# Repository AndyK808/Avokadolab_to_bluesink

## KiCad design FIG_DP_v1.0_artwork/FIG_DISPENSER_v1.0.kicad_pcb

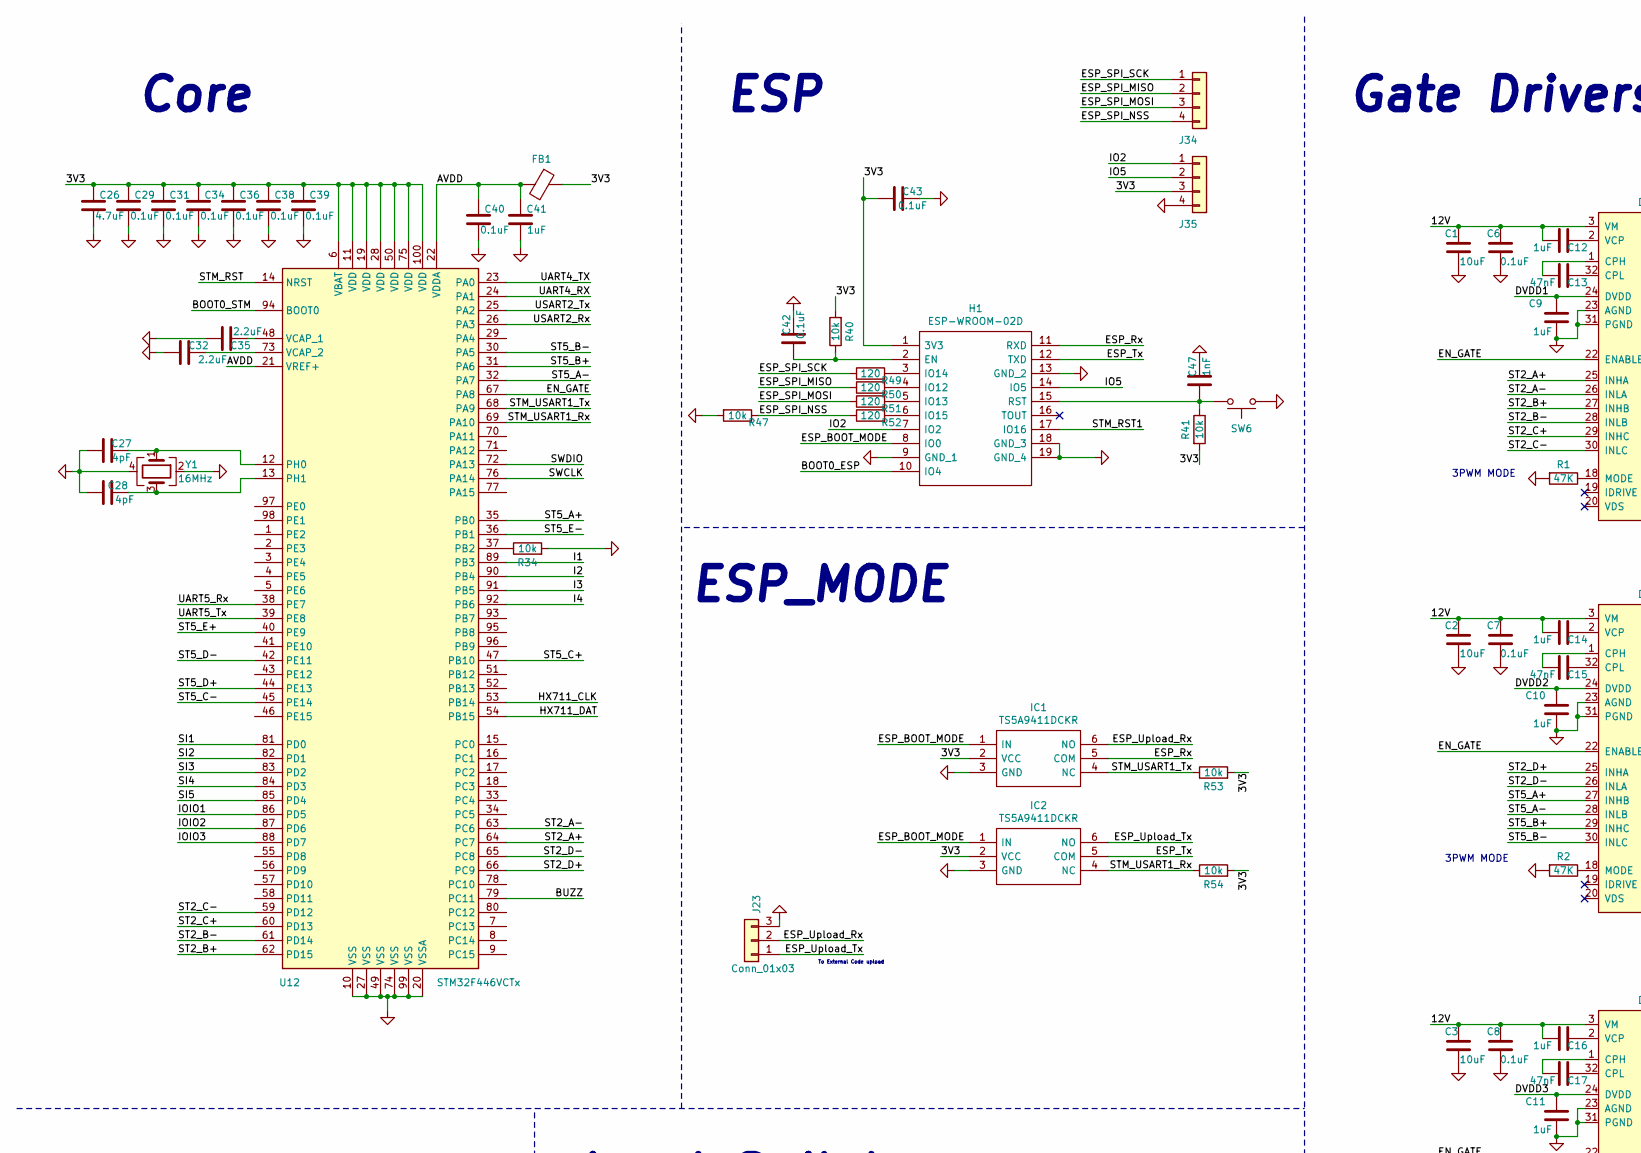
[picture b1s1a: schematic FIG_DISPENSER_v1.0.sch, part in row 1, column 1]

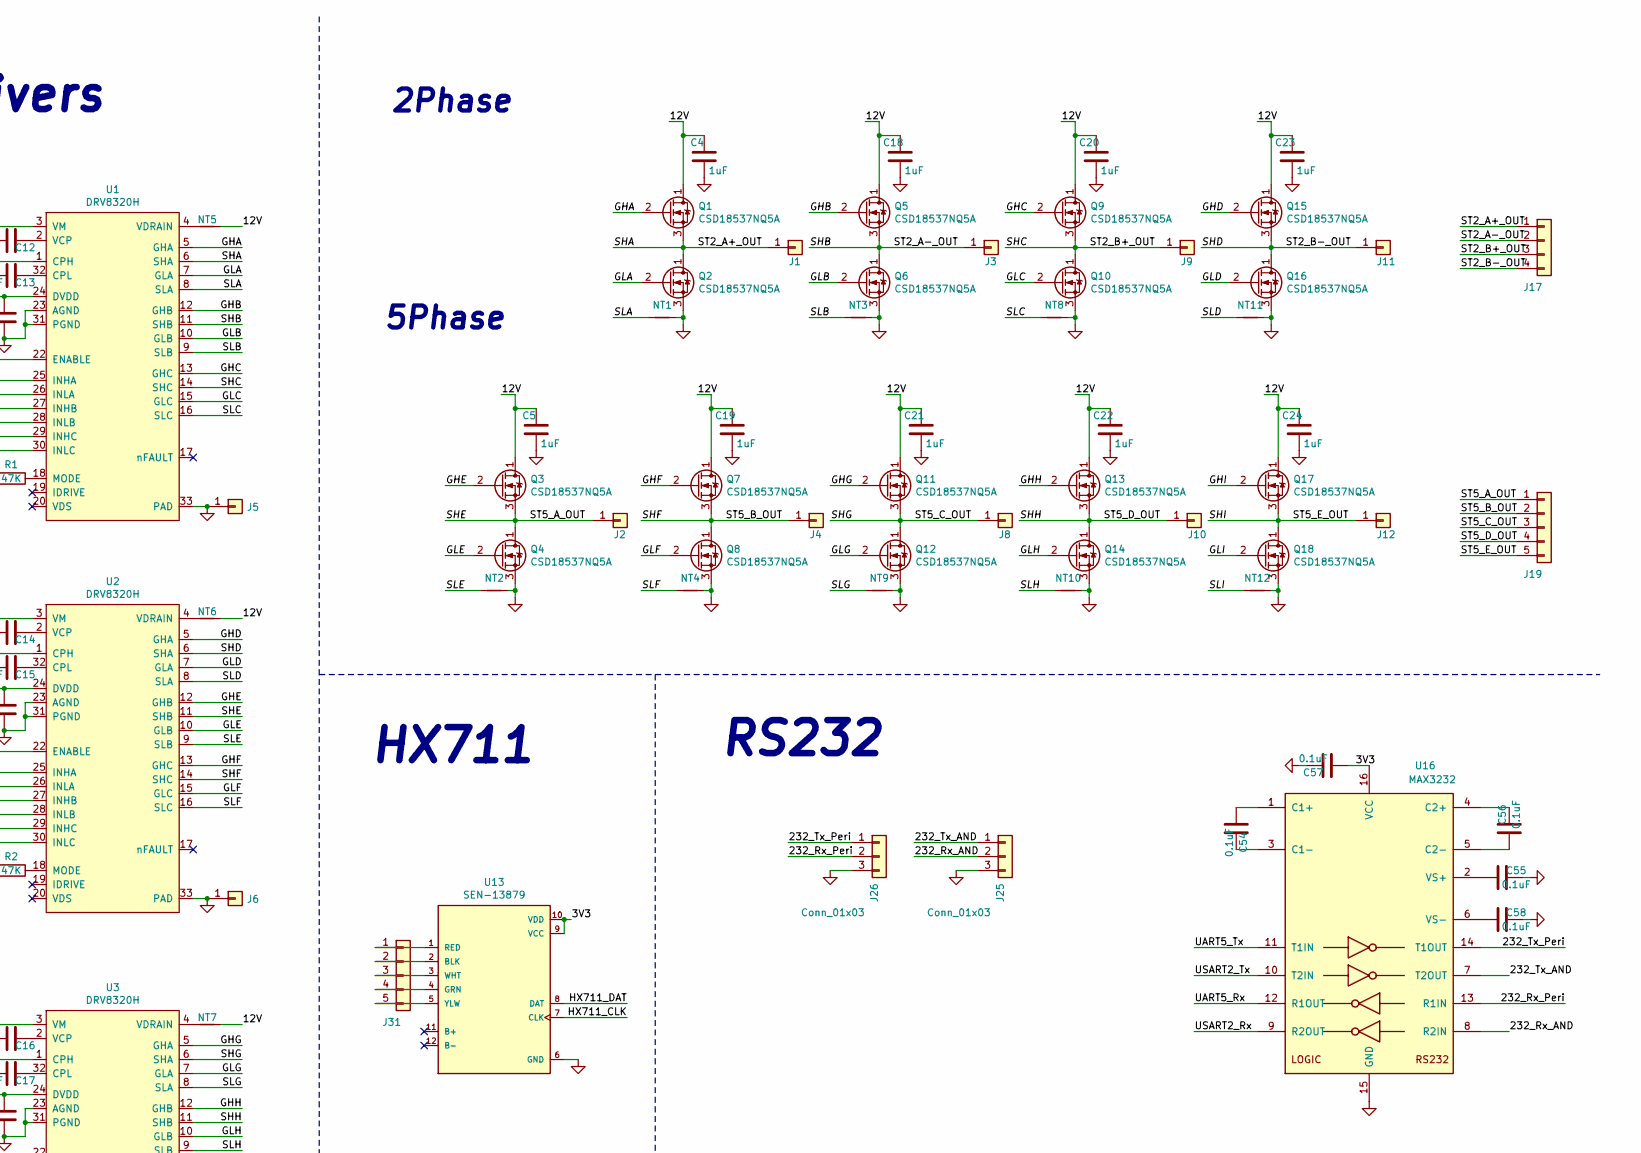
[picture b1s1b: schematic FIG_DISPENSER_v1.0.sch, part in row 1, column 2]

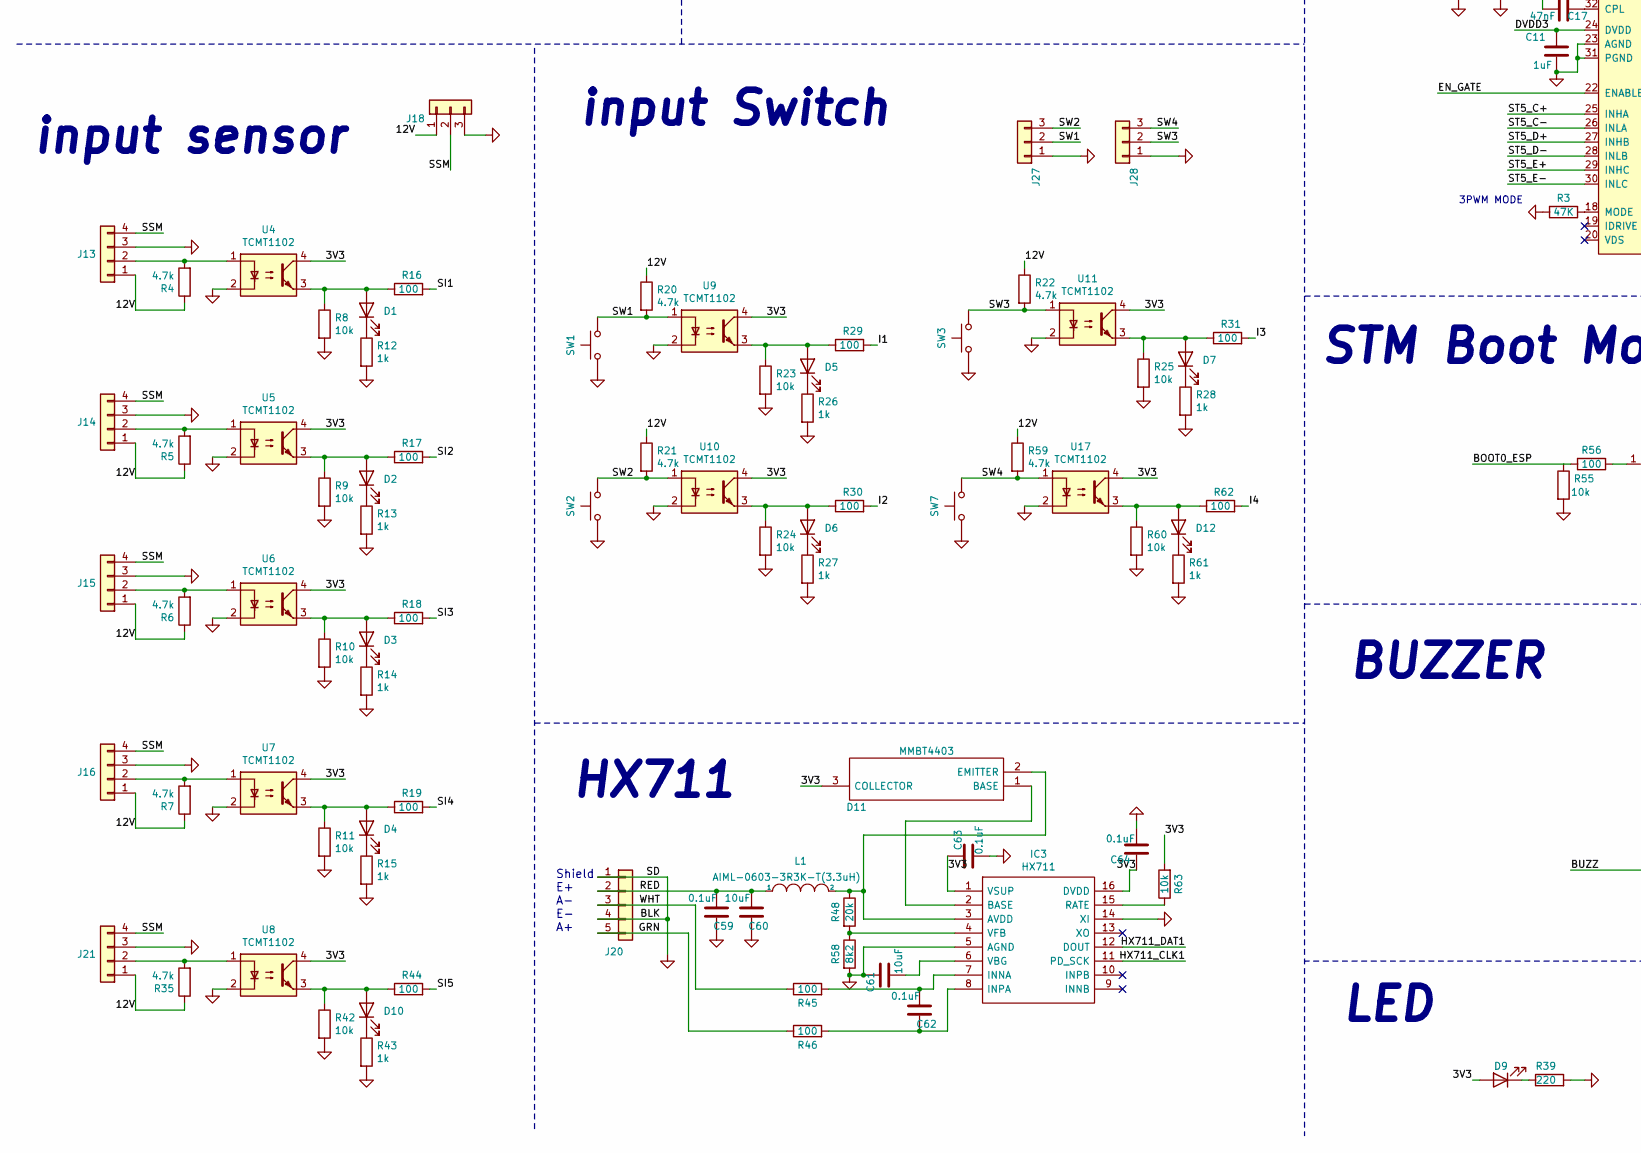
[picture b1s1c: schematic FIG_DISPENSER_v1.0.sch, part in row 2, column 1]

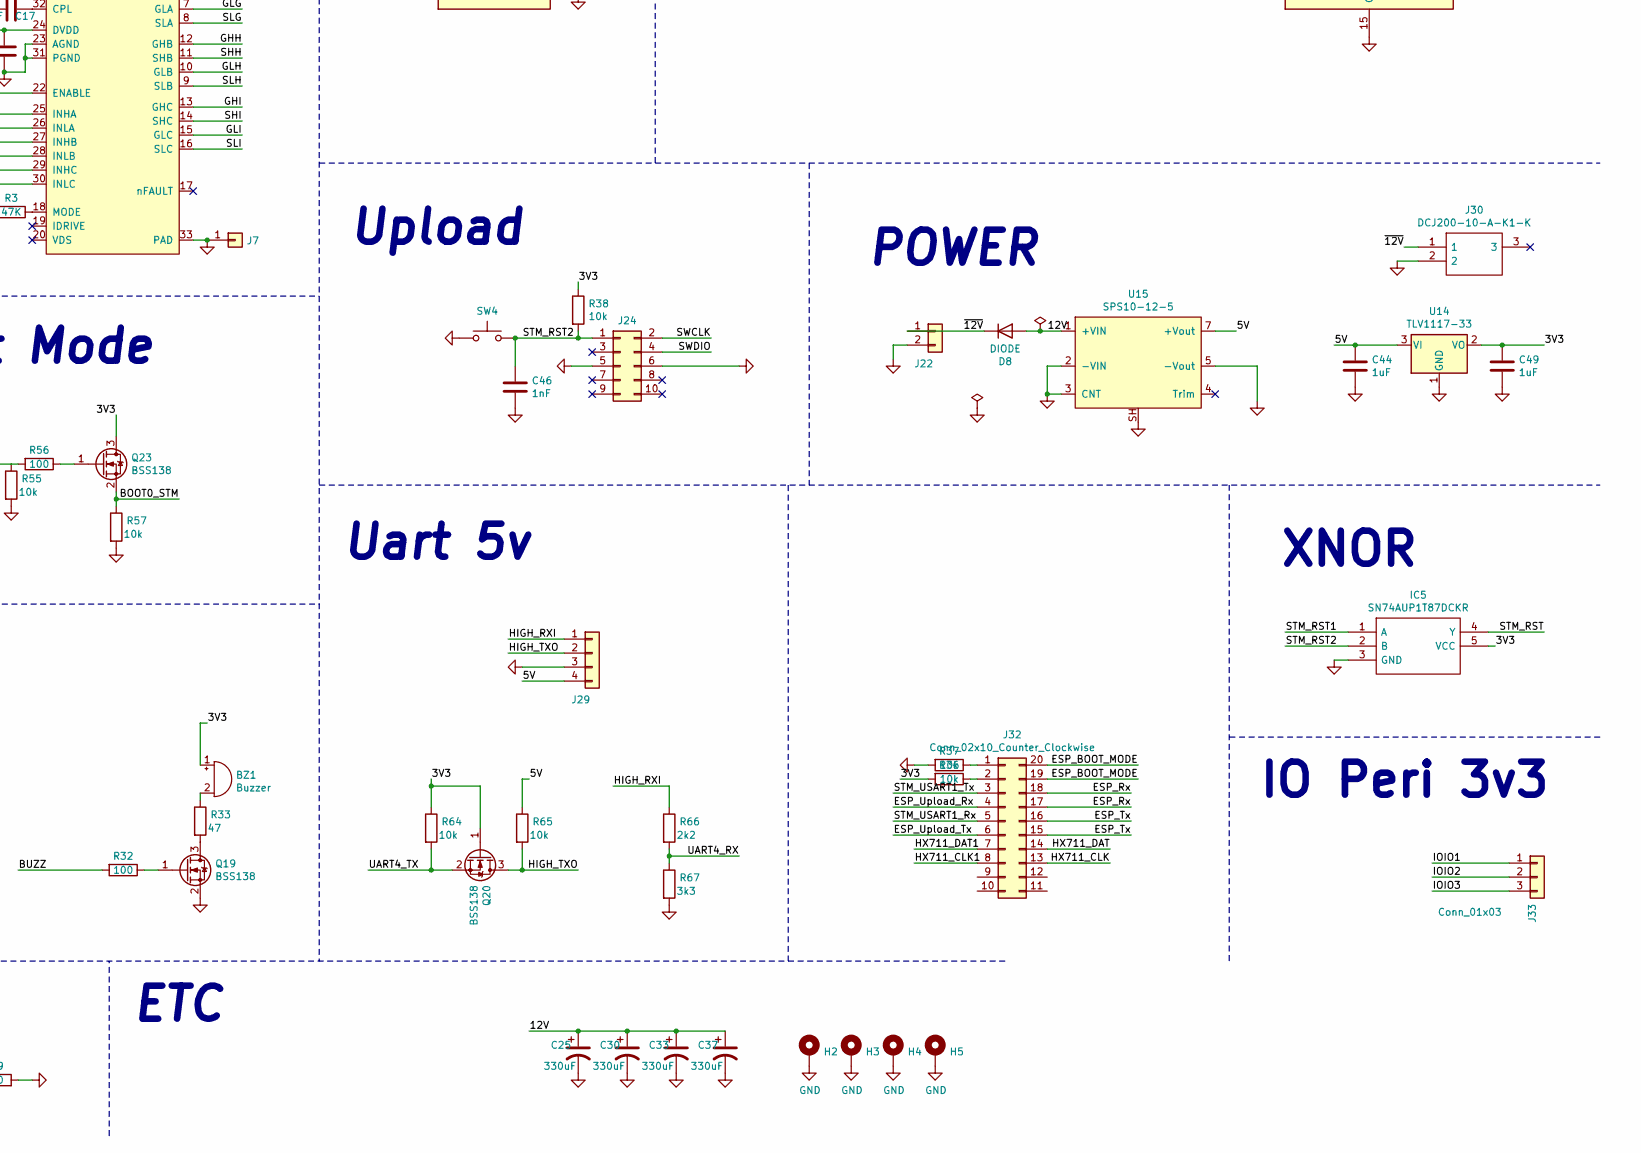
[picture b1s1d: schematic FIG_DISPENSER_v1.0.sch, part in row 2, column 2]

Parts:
BZ1: Buzzer; BUZZER
C1, C2, C3, C60, C61: 10uF; C_1206_3216Metric
C4, C5, C9, C10, C11, C12, C14, C16, C18, C19, C20, C21, C22, C23, C24, C44, C49: 1uF; C_0603_1608Metric
C6, C7, C8, C29, C42, C43, C54, C55, C56, C57, C58: 0.1uF; C_0603_1608Metric
C13, C15, C17: 47nF; C_0603_1608Metric
C25, C30, C33, C37: 330uF; CP_Radial_D10.0mm_P5.00mm
C26: 4.7uF; C_0603_1608Metric
C27, C28: 4pF; C_0603_1608Metric
C31, C34, C36, C38, C39, C40, C63, C64: 0.1uF; C_0402_1005Metric
C32, C35: 2.2uF; C_0603_1608Metric
C41: 1uF; C_0402_1005Metric
C46, C47: 1nF; C_0603_1608Metric
C59, C62: 0.1uF; C_1206_3216Metric
D1, D2, D3, D4, D5, D6, D7, D9, D10, D12: LED; LED_0603_1608Metric
D8: DIODE; D_DO-27_P15.24mm_Horizontal
D11: MMBT4403; SOT95P240X110-3N; Manufacturer_Part_Number MMBT4403; Mouser Part Number 583-MMBT4403
FB1: Ferrite_Bead; L_0603_1608Metric
H1: ESP-WROOM-02D; ESPWROOM02D; Manufacturer_Part_Number ESP-WROOM-02D; Mouser Part Number 356-ESPWROOM-02D
H2, H3, H4, H5: MountingHole_Pad; MountingHole_3mm_Pad_Via
IC1, IC2: TS5A9411DCKR; SOT65P210X110-6N; Mouser Part Number 595-TS5A9411DCKR
IC3: HX711; SOIC127P600X160-16N; Manufacturer_Part_Number HX711
IC5: SN74AUP1T87DCKR; SOT65P210X110-5N; Manufacturer_Part_Number SN74AUP1T87DCKR; Mouser Part Number 595-SN74AUP1T87DCKR
J1, J2, J3, J4, J5, J6, J7, J8, J9, J10, J11, J12: Conn_01x01; TestPoint_THTPad_D3.0mm_Drill1.5mm
J13, J14, J15, J16, J17, J21, J29, J34, J35: Conn_01x04; 5045-04
J18: Conn_01x03; PinHeader_1x03_P2.54mm_Vertical
J19, J20, J31: Conn_01x05; 5045-05
J22: Conn_01x02; LWB1143-02
J23, J25, J26, J27, J28, J33: Conn_01x03; 5045-03
J24: Conn_02x05_Odd_Even; IDC-Header_2x05_P2.54mm_Vertical
J30: DCJ200-10-A-K1-K; DCJ20010AK1K; Manufacturer_Part_Number DCJ200-10-A-K1-K
J32: Conn_02x10_Counter_Clockwise; slid_SW_SPST_10_array
L1: AIML-0603-3R3K-T(3.3uH); L_0603_1608Metric
NT1, NT2, NT3, NT4, NT5, NT6, NT7, NT8, NT9, NT10, NT11, NT12: Net-Tie_2; NET_TIE_0_25
Q1, Q2, Q3, Q4, Q5, Q6, Q7, Q8, Q9, Q10, Q11, Q12, Q13, Q14, Q15, Q16, Q17, Q18: CSD18537NQ5A
Q19, Q20, Q23: BSS138; SOT-23
R1, R2, R3: 47K; R_0603_1608Metric
R4, R5, R6, R7, R20, R21, R22, R35, R59: 4.7k; R_0603_1608Metric
R8, R9, R10, R11, R23, R24, R25, R34, R36, R37, R38, R40, R41, R42, R47, R53, R54, R55, R57, R60, R63, R64, R65: 10k; R_0603_1608Metric
R12, R13, R14, R15, R26, R27, R28, R43, R61: 1k; R_0603_1608Metric
R16, R17, R18, R19, R29, R30, R31, R32, R44, R45, R46, R56, R62: 100; R_0603_1608Metric
R33: 47; R_0603_1608Metric
R39: 220; R_0603_1608Metric
R48: 20k; R_0603_1608Metric
R49, R50, R51, R52: 120; R_0603_1608Metric
R58: 8k2; R_0603_1608Metric
R66: 2k2; R_0603_1608Metric
R67: 3k3; R_0603_1608Metric
SW1, SW2, SW3, SW4, SW6, SW7: SW_Push; SW_PUSH_6mm_H5mm
U1, U2, U3: DRV8320H; TI-PWQFN-N32
U4, U5, U6, U7, U8, U9, U10, U11, U17: TCMT1102; SOP-4_4.4x2.6mm_P1.27mm
U12: STM32F446VCTx; LQFP-100_14x14mm_P0.5mm
U13: SEN-13879; SPARKFUN_SEN-13879; Digi-Key_Part_Number 1568-1436-ND
U14: TLV1117-33; SOT-223-3_TabPin2
U15: SPS10-12-5
U16: MAX3232; SOIC-16_3.9x9.9mm_P1.27mm
Y1: 16MHz; ABM8

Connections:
/3V3: BZ1.1 (-), C26.1, C29.1, C31.1, C34.1, C36.1, C38.1, C39.1, C43.2, C49.1, C57.2, C63.1, C64.1, D9.2 (A), D11.3 (COLLECTOR), FB1.1, H1.1 (3V3), IC1.2 (VCC), IC2.2 (VCC), IC3.1 (VSUP), IC3.16 (DVDD), IC5.5 (VCC), J35.3, Q20.1 (G), Q23.3 (D), R36.2, R38.1, R40.2, R41.2, R53.2, R54.2, R63.2, R64.1, U4.4, U5.4, U6.4, U7.4, U8.4, U9.4, U10.4, U11.4, U12.6 (VBAT), U12.11 (VDD), U12.19 (VDD), U12.28 (VDD), U12.50 (VDD), U12.75 (VDD), U12.100 (VDD), U13.9 (VCC), U13.10 (VDD), U14.2 (VO), U16.16 (VCC), U17.4
/5V: C44.1, J29.4, R65.1, U14.3 (VI), U15.7 (+Vout)
/12V: C1.1, C2.1, C3.1, C4.1, C5.1, C6.1, C7.1, C8.1, C12.1, C14.1, C16.1, C18.1, C19.1, C20.1, C21.1, C22.1, C23.1, C24.1, C25.1, C30.1, C33.1, C37.1, D8.1 (A), J13.1, J14.1, J15.1, J16.1, J18.1, J21.1, NT5.2, NT6.2, NT7.2, Q1.1 (D), Q3.1 (D), Q5.1 (D), Q7.1 (D), Q9.1 (D), Q11.1 (D), Q13.1 (D), Q15.1 (D), Q17.1 (D), R4.1, R5.1, R6.1, R7.1, R20.1, R21.1, R22.1, R35.1, R59.1, U1.3 (VM), U2.3 (VM), U3.3 (VM), U15.1 (+VIN)
/232_Rx_AND: J25.2, U16.8 (R2IN)
/232_Rx_Peri: J26.2, U16.13 (R1IN)
/232_Tx_AND: J25.1, U16.7 (T2OUT)
/232_Tx_Peri: J26.1, U16.14 (T1OUT)
/AVDD: C40.1, C41.1, FB1.2, U12.21 (VREF+), U12.22 (VDDA)
/BOOT0_ESP: H1.10 (IO4), R55.1, R56.2
/BOOT0_STM: Q23.2 (S), R57.1, U12.94 (BOOT0)
/BUZZ: R32.2, U12.79 (PC11)
/DVDD1: C9.1, U1.24 (DVDD)
/DVDD2: C10.1, U2.24 (DVDD)
/DVDD3: C11.1, U3.24 (DVDD)
/EN_GATE: U1.22 (ENABLE), U2.22 (ENABLE), U3.22 (ENABLE), U12.67 (PA8)
/ESP_BOOT_MODE: H1.8 (IO0), IC1.1 (IN), IC2.1 (IN), J32.19, J32.20
/ESP_Rx: H1.11 (RXD), IC1.5 (COM), J32.17, J32.18
/ESP_SPI_MISO: J34.2, R50.1
/ESP_SPI_MOSI: J34.3, R51.1
/ESP_SPI_NSS: J34.4, R47.1, R52.1
/ESP_SPI_SCK: J34.1, R49.1
/ESP_Tx: H1.12 (TXD), IC2.5 (COM), J32.15, J32.16
/ESP_Upload_Rx: IC1.6 (NO), J23.2, J32.4
/ESP_Upload_Tx: IC2.6 (NO), J23.1, J32.6
/GHA: Q1.2 (G), U1.5 (GHA)
/GHB: Q5.2 (G), U1.12 (GHB)
/GHC: Q9.2 (G), U1.13 (GHC)
/GHD: Q15.2 (G), U2.5 (GHA)
/GHE: Q3.2 (G), U2.12 (GHB)
/GHF: Q7.2 (G), U2.13 (GHC)
/GHG: Q11.2 (G), U3.5 (GHA)
/GHH: Q13.2 (G), U3.12 (GHB)
/GHI: Q17.2 (G), U3.13 (GHC)
/GLA: Q2.2 (G), U1.7 (GLA)
/GLB: Q6.2 (G), U1.10 (GLB)
/GLC: Q10.2 (G), U1.15 (GLC)
/GLD: Q16.2 (G), U2.7 (GLA)
/GLE: Q4.2 (G), U2.10 (GLB)
/GLF: Q8.2 (G), U2.15 (GLC)
/GLG: Q12.2 (G), U3.7 (GLA)
/GLH: Q14.2 (G), U3.10 (GLB)
/GLI: Q18.2 (G), U3.15 (GLC)
/GRN: J20.5, R46.1
/HIGH_RXI: J29.1, R66.1
/HIGH_TXO: J29.2, Q20.3 (D), R65.2
/HX711_CLK: J32.13, U12.53 (PB14), U13.7 (CLK)
/HX711_CLK1: IC3.11 (PD_SCK), J32.8
/HX711_DAT: J32.14, U12.54 (PB15), U13.8 (DAT)
/HX711_DAT1: IC3.12 (DOUT), J32.7
/I1: R29.2, U12.89 (PB3)
/I2: R30.2, U12.90 (PB4)
/I3: R31.2, U12.91 (PB5)
/I4: R62.2, U12.92 (PB6)
/IO2: H1.7 (IO2), J35.1
/IO5: H1.14 (IO5), J35.2
/IOIO1: J33.1, U12.86 (PD5)
/IOIO2: J33.2, U12.87 (PD6)
/IOIO3: J33.3, U12.88 (PD7)
/RED: C59.2, C60.2, J20.2, L1.1
/SHA: J1.1, J17.1, Q1.3 (S), Q2.1 (D), U1.6 (SHA)
/SHB: J3.1, J17.2, Q5.3 (S), Q6.1 (D), U1.11 (SHB)
/SHC: J9.1, J17.3, Q9.3 (S), Q10.1 (D), U1.14 (SHC)
/SHD: J11.1, J17.4, Q15.3 (S), Q16.1 (D), U2.6 (SHA)
/SHE: J2.1, J19.1, Q3.3 (S), Q4.1 (D), U2.11 (SHB)
/SHF: J4.1, J19.2, Q7.3 (S), Q8.1 (D), U2.14 (SHC)
/SHG: J8.1, J19.3, Q11.3 (S), Q12.1 (D), U3.6 (SHA)
/SHH: J10.1, J19.4, Q13.3 (S), Q14.1 (D), U3.11 (SHB)
/SHI: J12.1, J19.5, Q17.3 (S), Q18.1 (D), U3.14 (SHC)
/SI1: R16.2, U12.81 (PD0)
/SI2: R17.2, U12.82 (PD1)
/SI3: R18.2, U12.83 (PD2)
/SI4: R19.2, U12.84 (PD3)
/SI5: R44.2, U12.85 (PD4)
/SLA: NT1.1, U1.8 (SLA)
/SLB: NT3.1, U1.9 (SLB)
/SLC: NT8.1, U1.16 (SLC)
/SLD: NT11.1, U2.8 (SLA)
/SLE: NT2.1, U2.9 (SLB)
/SLF: NT4.1, U2.16 (SLC)
/SLG: NT9.1, U3.8 (SLA)
/SLH: NT10.1, U3.9 (SLB)
/SLI: NT12.1, U3.16 (SLC)
/SSM: J13.4, J14.4, J15.4, J16.4, J18.2, J21.4
/ST2_A+: U1.25 (INHA), U12.64 (PC7)
/ST2_A-: U1.26 (INLA), U12.63 (PC6)
/ST2_B+: U1.27 (INHB), U12.62 (PD15)
/ST2_B-: U1.28 (INLB), U12.61 (PD14)
/ST2_C+: U1.29 (INHC), U12.60 (PD13)
/ST2_C-: U1.30 (INLC), U12.59 (PD12)
/ST2_D+: U2.25 (INHA), U12.66 (PC9)
/ST2_D-: U2.26 (INLA), U12.65 (PC8)
/ST5_A+: U2.27 (INHB), U12.35 (PB0)
/ST5_A-: U2.28 (INLB), U12.32 (PA7)
/ST5_B+: U2.29 (INHC), U12.31 (PA6)
/ST5_B-: U2.30 (INLC), U12.30 (PA5)
/ST5_C+: U3.25 (INHA), U12.47 (PB10)
/ST5_C-: U3.26 (INLA), U12.45 (PE14)
/ST5_D+: U3.27 (INHB), U12.44 (PE13)
/ST5_D-: U3.28 (INLB), U12.42 (PE11)
/ST5_E+: U3.29 (INHC), U12.40 (PE9)
/ST5_E-: U3.30 (INLC), U12.36 (PB1)
/STM_RST: IC5.4 (Y), U12.14 (NRST)
/STM_RST1: H1.17 (IO16), IC5.1 (A)
/STM_USART1_Rx: IC2.4 (NC), J32.5, R54.1, U12.69 (PA10)
/STM_USART1_Tx: IC1.4 (NC), J32.3, R53.1, U12.68 (PA9)
/SW1: J27.2, R20.2, SW1.2, U9.1
/SW2: J27.3, R21.2, SW2.2, U10.1
/SW3: J28.2, R22.2, SW3.2, U11.1
/SWCLK: J24.2, U12.76 (PA14)
/SWDIO: J24.4, U12.72 (PA13)
/UART4_RX: R66.2, R67.1, U12.24 (PA1)
/UART4_TX: Q20.2 (S), R64.2, U12.23 (PA0)
/UART5_Rx: U12.38 (PE7), U16.12 (R1OUT)
/UART5_Tx: U12.39 (PE8), U16.11 (T1IN)
/USART2_Rx: U12.26 (PA3), U16.9 (R2OUT)
/USART2_Tx: U12.25 (PA2), U16.10 (T2IN)
/WHT: J20.3, R45.1
/~12V: D8.2 (K), J22.1, J30.1
GND: C1.2, C2.2, C3.2, C4.2, C5.2, C6.2, C7.2, C8.2, C9.2, C10.2, C11.2, C18.2, C19.2, C20.2, C21.2, C22.2, C23.2, C24.2, C25.2, C26.2, C27.2, C28.1, C29.2, C30.2, C31.2, C32.2, C33.2, C34.2, C35.2, C36.2, C37.2, C38.2, C39.2, C40.2, C41.2, C42.1, C43.1, C44.2, C46.2, C47.1, C49.2, C55.1, C57.1, C58.1, C59.1, C60.1, C61.1, C63.2, C64.2, H1.9 (GND_1), H1.13 (GND_2), H1.18 (GND_3), H1.19 (GND_4), H2.1, H3.1, H4.1, H5.1, IC1.3 (GND), IC2.3 (GND), IC3.5 (AGND), IC3.14 (XI), IC5.3 (GND), J5.1, J6.1, J7.1, J13.3, J14.3, J15.3, J16.3, J18.3, J20.1, J20.4, J21.3, J22.2, J23.3, J24.5, J24.6, J25.3, J26.3, J27.1, J28.1, J29.3, J30.2, J35.4, NT1.2, NT2.2, NT3.2, NT4.2, NT8.2, NT9.2, NT10.2, NT11.2, NT12.2, Q2.3 (S), Q4.3 (S), Q6.3 (S), Q8.3 (S), Q10.3 (S), Q12.3 (S), Q14.3 (S), Q16.3 (S), Q18.3 (S), Q19.2 (S), R1.2, R2.2, R3.2, R8.2, R9.2, R10.2, R11.2, R12.2, R13.2, R14.2, R15.2, R23.2, R24.2, R25.2, R26.2, R27.2, R28.2, R34.2, R37.2, R39.2, R42.2, R43.2, R47.2, R55.2, R57.2, R58.2, R60.2, R61.2, R67.2, SW1.1, SW2.1, SW3.1, SW4.1, SW6.1, SW7.1, U1.23 (AGND), U1.31 (PGND), U1.33 (PAD), U2.23 (AGND), U2.31 (PGND), U2.33 (PAD), U3.23 (AGND), U3.31 (PGND), U3.33 (PAD), U4.2, U5.2, U6.2, U7.2, U8.2, U9.2, U10.2, U11.2, U12.10 (VSS), U12.20 (VSSA), U12.27 (VSS), U12.49 (VSS), U12.74 (VSS), U12.99 (VSS), U13.6 (GND), U14.1 (GND), U15.2 (-VIN), U15.3 (CNT), U15.5 (-Vout), U15.SH, U16.15 (GND), U17.2, Y1.2, Y1.4; also elsewhere on the board
unnamed: BZ1.2 (+), R33.1
unnamed: C12.2, U1.2 (VCP)
unnamed: C13.1, U1.1 (CPH)
unnamed: C13.2, U1.32 (CPL)
unnamed: C14.2, U2.2 (VCP)
unnamed: C15.1, U2.1 (CPH)
unnamed: C15.2, U2.32 (CPL)
unnamed: C16.2, U3.2 (VCP)
unnamed: C17.1, U3.1 (CPH)
unnamed: C17.2, U3.32 (CPL)
unnamed: C27.1, U12.12 (PH0), Y1.1
unnamed: C28.2, U12.13 (PH1), Y1.3
unnamed: C32.1, U12.73 (VCAP_2)
unnamed: C35.1, U12.48 (VCAP_1)
unnamed: C42.2, H1.2 (EN), R40.1
unnamed: C47.2, H1.15 (RST), R41.1, SW6.2
unnamed: C54.1, U16.3 (C1-)
unnamed: C54.2, U16.1 (C1+)
unnamed: C55.2, U16.2 (VS+)
unnamed: C56.1, U16.4 (C2+)
unnamed: C56.2, U16.5 (C2-)
unnamed: C58.2, U16.6 (VS-)
unnamed: C61.2, IC3.6 (VBG)
unnamed: C62.1, IC3.8 (INPA), R46.2
unnamed: C62.2, IC3.7 (INNA), R45.2
unnamed: D1.1 (K), R12.1
unnamed: D1.2 (A), R8.1, R16.1, U4.3
unnamed: D2.1 (K), R13.1
unnamed: D2.2 (A), R9.1, R17.1, U5.3
unnamed: D3.1 (K), R14.1
unnamed: D3.2 (A), R10.1, R18.1, U6.3
unnamed: D4.1 (K), R15.1
unnamed: D4.2 (A), R11.1, R19.1, U7.3
unnamed: D5.1 (K), R26.1
unnamed: D5.2 (A), R23.1, R29.1, U9.3
unnamed: D6.1 (K), R27.1
unnamed: D6.2 (A), R24.1, R30.1, U10.3
unnamed: D7.1 (K), R28.1
unnamed: D7.2 (A), R25.1, R31.1, U11.3
unnamed: D9.1 (K), R39.1
unnamed: D10.1 (K), R43.1
unnamed: D10.2 (A), R42.1, R44.1, U8.3
unnamed: D11.1 (BASE), IC3.2 (BASE)
unnamed: D11.2 (EMITTER), IC3.3 (AVDD), L1.2, R48.1
unnamed: D12.1 (K), R61.1
unnamed: D12.2 (A), R60.1, R62.1, U17.3
unnamed: H1.3 (IO14), R49.2
unnamed: H1.4 (IO12), R50.2
unnamed: H1.5 (IO13), R51.2
unnamed: H1.6 (IO15), R52.2
unnamed: IC3.4 (VFB), R48.2, R58.1
unnamed: IC3.15 (RATE), R63.1
unnamed: J13.2, R4.2, U4.1
unnamed: J14.2, R5.2, U5.1
unnamed: J15.2, R6.2, U6.1
unnamed: J16.2, R7.2, U7.1
unnamed: J21.2, R35.2, U8.1
unnamed: J31.1, U13.1 (RED)
unnamed: J31.2, U13.2 (BLK)
unnamed: J31.3, U13.3 (WHT)
unnamed: J31.4, U13.4 (GRN)
unnamed: J31.5, U13.5 (YLW)
unnamed: J32.1, R37.1
unnamed: J32.2, R36.1
unnamed: NT5.1, U1.4 (VDRAIN)
unnamed: NT6.1, U2.4 (VDRAIN)
unnamed: NT7.1, U3.4 (VDRAIN)
unnamed: Q19.1 (G), R32.1
unnamed: Q19.3 (D), R33.2
unnamed: Q23.1 (G), R56.1
unnamed: R1.1, U1.18 (MODE)
unnamed: R2.1, U2.18 (MODE)
unnamed: R3.1, U3.18 (MODE)
unnamed: R34.1, U12.37 (PB2)

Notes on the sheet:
Gate Drivers
input sensor
POWER
LED
Core
2Phase
5Phase
Upload
ETC
BUZZER
input Switch
HX711
To External Code upload
3PWM MODE
ESP
RS232
STM Boot Mode
Uart 5v
Shield E+ A- E- A+
XNOR
ESP_MODE
IO Peri 3v3

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
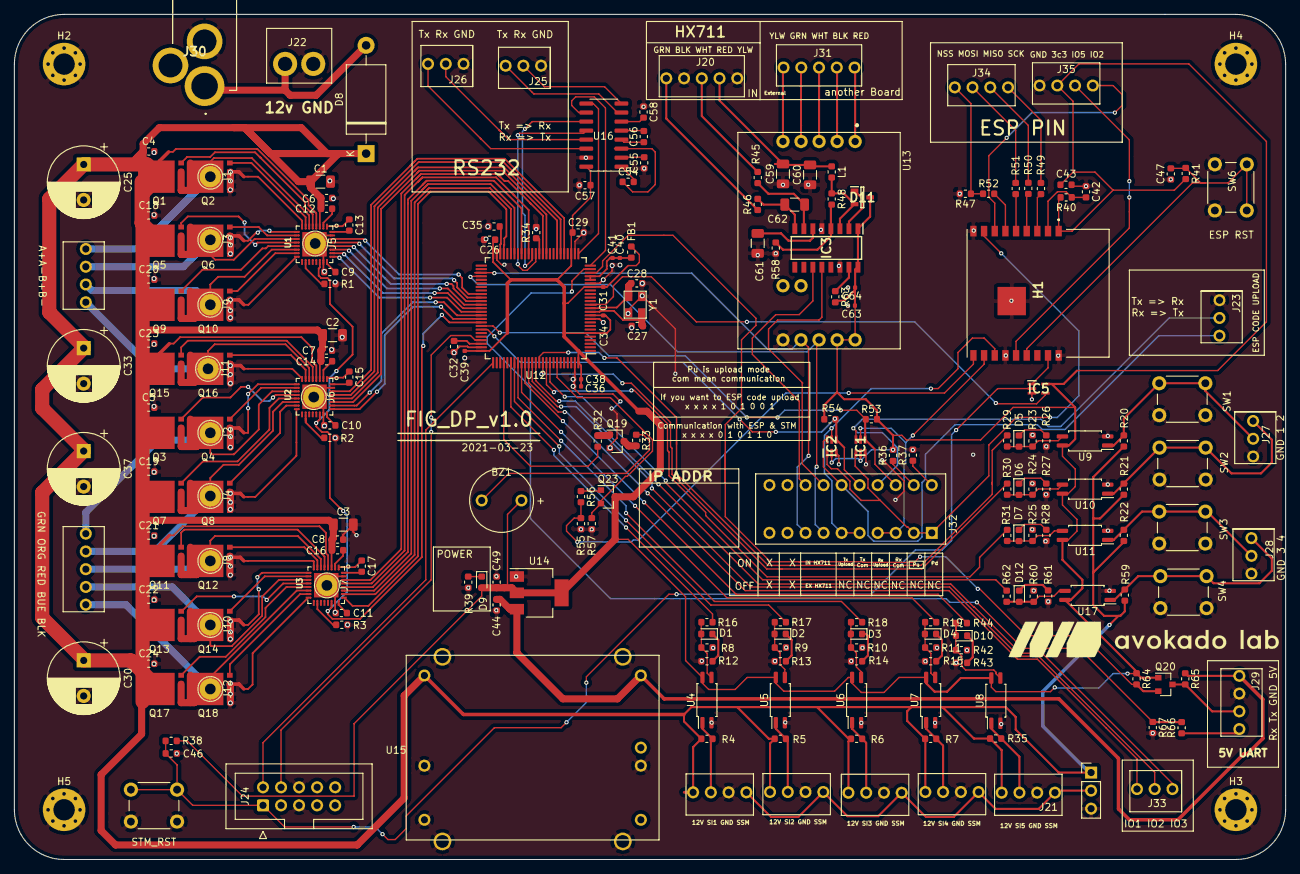
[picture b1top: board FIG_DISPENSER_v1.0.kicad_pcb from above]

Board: 2 copper layers, 179.0 x 119.0 mm, 241 parts (0 on the bottom side), 195 nets.

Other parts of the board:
STM_RST: SW_Push; SW_PUSH_6mm_H5mm

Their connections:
GND: STM_RST.1; also elsewhere on the board
